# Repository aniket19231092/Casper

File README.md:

# Casper
Converting a telescope into one that automatically positions itself to view planets and other celestial bodies based on user input.
2 Stepper motor axis will position its azimuth, basically cardinal direction, and altitude, the angle between the horizon and straight up. To find the target a camera on the telescope tube will take pictures of the sky and use plate solving, which is where the position of the stars in the sky are compared to a database of known stars to find the coordinates of where in the sky the telescope is pointing. A Raspberry Pi will handle the bulk of the computing while a microcontroller drives the stepper motors. A belt system will be used to gain gear reduction between the stepper motors and the load shaft.
This project is split into 3 parts, mechanical, electrical, and software. On the electrical side I am making a custom PCB controller for the telescope. This includes a STM32 microcontroller, Raspberry Pi 0 2W, stepper motor drivers, power regulators, and all other supporting hardware.
The mechanical part will be designing a mechanical drive system for both axes out of commercially available parts and custom 3D printed parts.
On the software side, the Raspberry Pi will run the plate solving software and tell the microcontroller how much to move each motor. The Pi will also host an interface where user commands can be sent to operate the telescope.

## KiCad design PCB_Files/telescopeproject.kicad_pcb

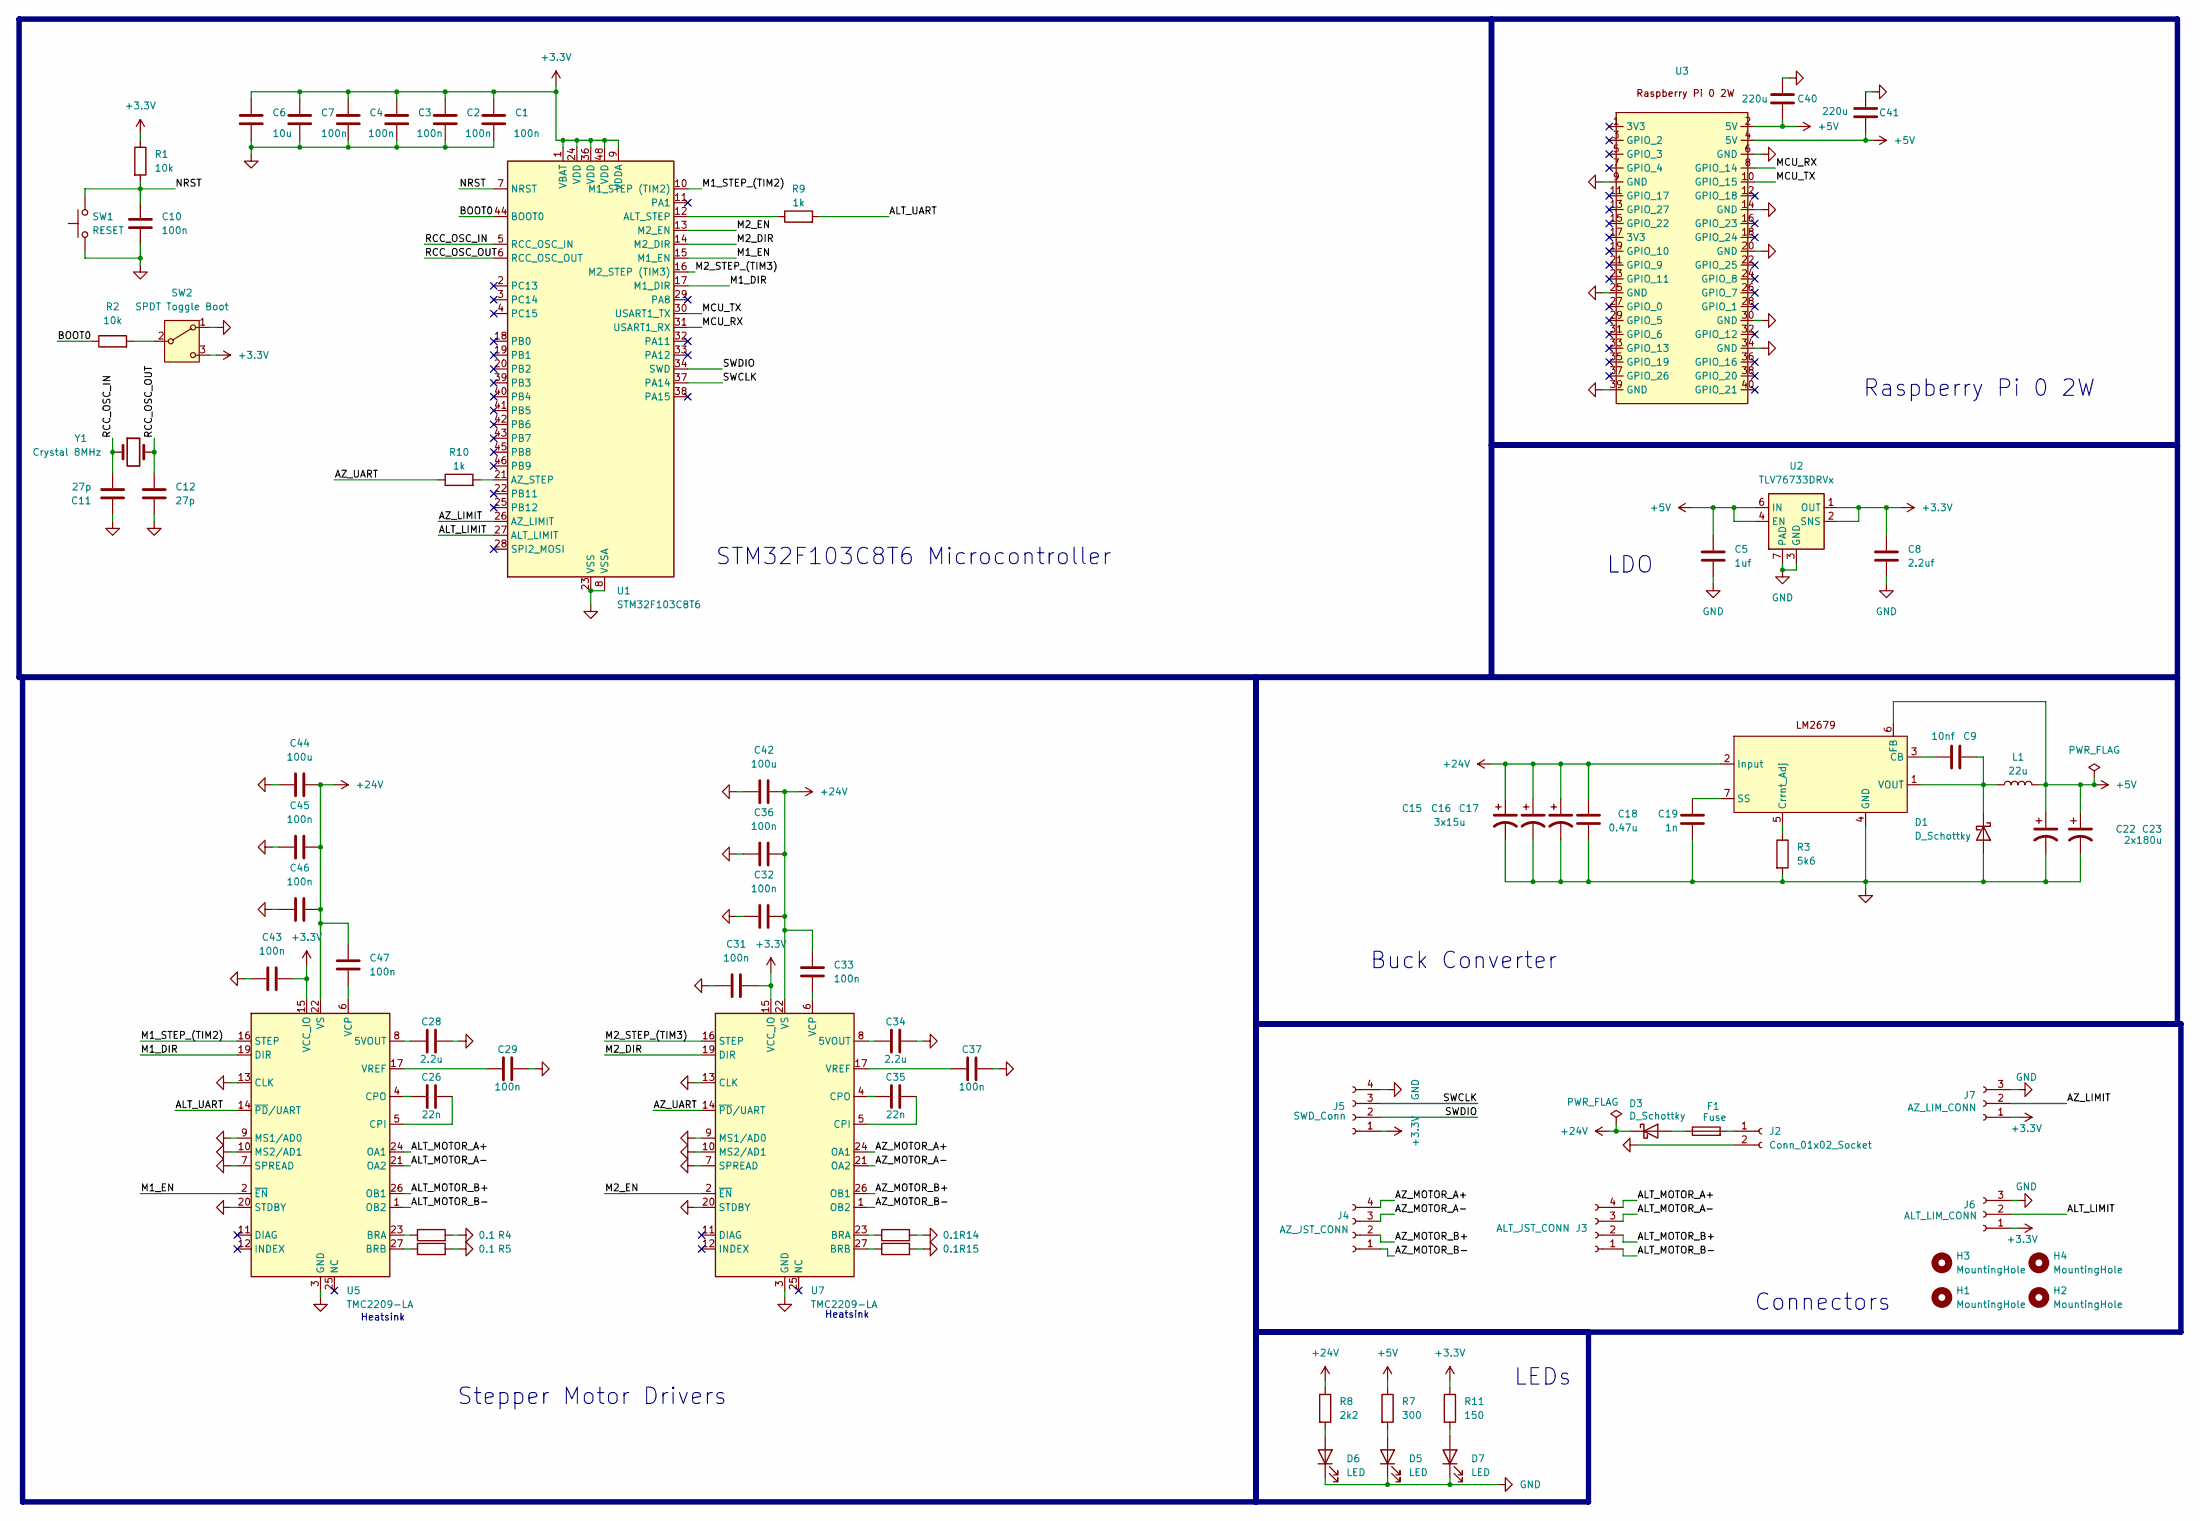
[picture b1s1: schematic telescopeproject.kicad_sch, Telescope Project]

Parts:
C1, C2, C3, C4, C7, C10, C29, C31, C32, C33, C36, C37, C43, C45, C46, C47: 100n; C_0603_1608Metric
C5: 1uf; C_1210_3225Metric
C6: 10u; C_Elec_5x5.4
C8: 2.2uf; C_1210_3225Metric
C9: 10nf; C_0603_1608Metric
C11, C12: 27p; C_0603_1608Metric
C15: 3x15u; CP_Elec_6.3x5.4
C16, C17: 15u; CP_Elec_6.3x5.4
C18: 0.47u; C_Elec_4x5.4
C19: 1n; C_0603_1608Metric
C22, C23: 2x180u; CP_Radial_D6.3mm_P2.50mm
C26, C35: 22n; C_0603_1608Metric
C28, C34: 2.2u; C_Elec_4x5.4
C40, C41: 220u; C_Radial_D10.0mm_H16.0mm_P5.00mm
C42, C44: 100u; C_Radial_D8.0mm_H7.0mm_P3.50mm
D1, D3: D_Schottky; TO-263-2
D5, D6, D7: LED; LED_0603_1608Metric
F1: Fuse; 30R800UH
H1, H2, H3, H4: MountingHole; MountingHole_3.2mm_M3_ISO14580_Pad
J2: Conn_01x02_Socket; B2PSVHLFSN
J3: ALT_JST_CONN; CONN_B4PS-VH_JST
J4: AZ_JST_CONN; CONN_B4PS-VH_JST
J5: SWD_Conn; PinHeader_1x04_P2.54mm_Horizontal
J6: ALT_LIM_CONN; CONN03_B3PS-VH_JST
J7: AZ_LIM_CONN; CONN03_B3PS-VH_JST
L1: 22u; D2PAK_STM
R1, R2: 10k; R_0603_1608Metric
R3: 5k6; R_0603_1608Metric
R4, R5, R14, R15: 0.1; R_2512_6332Metric
R7: 300; R_0603_1608Metric
R8: 2k2; R_0603_1608Metric
R9, R10: 1k; R_0603_1608Metric
R11: 150; R_0603_1608Metric
SW1: RESET; SW_PUSH_6mm_H4.3mm
SW2: SPDT Toggle Boot; PinHeader_1x03_P2.54mm_Vertical
U1: STM32F103C8T6; LQFP-48_7x7mm_P0.5mm
U2: TLV76733DRVx; WSON-6-1EP_2x2mm_P0.65mm_EP1x1.6mm_ThermalVias
U3: PinHeader_2x20_P2.54mm_Vertical
U5, U7: TMC2209-LA; VQFN-28-1EP_5x5mm_P0.5mm_EP3.7x3.7mm
U6: TO-220-7_P2.54x5.08mm_StaggerOdd_Lead3.08mm_Vertical
Y1: Crystal 8MHz; Crystal_SMD_Abracon_ABM3-2Pin_5.0x3.2mm

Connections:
+3.3V: C1.1, C2.1, C3.1, C4.1, C6.1, C7.1, C8.1, C31.2, C43.2, J5.1, J6.1, J7.1, R1.1, R11.1, SW2.3 (C), U1.1 (VBAT), U1.9 (VDDA), U1.24 (VDD), U1.36 (VDD), U1.48 (VDD), U2.1 (OUT), U2.2 (SNS), U5.15 (VCC_IO), U7.15 (VCC_IO)
+5V: C5.1, C22.1, C23.1, C40.2, C41.2, L1.2, R7.1, U2.4 (EN), U2.6 (IN), U3.2 (5V), U3.4 (5V), U6.6 (FB)
+24V: C15.1, C16.1, C17.1, C18.1, C32.2, C33.2, C36.2, C42.2, C44.2, C45.2, C46.2, C47.2, D3.1 (K), R8.1, U5.22 (VS), U5.28 (VS), U6.2 (Input), U7.22 (VS), U7.28 (VS)
/ALT_LIMIT: J6.2, U1.27 (ALT_LIMIT)
/ALT_MOTOR_A+: J3.4, U5.24 (OA1)
/ALT_MOTOR_A-: J3.3, U5.21 (OA2)
/ALT_MOTOR_B+: J3.2, U5.26 (OB1)
/ALT_MOTOR_B-: J3.1, U5.1 (OB2)
/ALT_UART: R9.2, U5.14 (~PD/UART)
/AZ_LIMIT: J7.2, U1.26 (AZ_LIMIT)
/AZ_MOTOR_A+: J4.4, U7.24 (OA1)
/AZ_MOTOR_A-: J4.3, U7.21 (OA2)
/AZ_MOTOR_B+: J4.2, U7.26 (OB1)
/AZ_MOTOR_B-: J4.1, U7.1 (OB2)
/AZ_UART: R10.1, U7.14 (~PD/UART)
/BOOT0: R2.1, U1.44 (BOOT0)
/M1_DIR: U1.17 (M1_DIR), U5.19 (DIR)
/M1_EN: U1.15 (M1_EN), U5.2 (~EN)
/M1_STEP_(TIM2): U1.10 (M1_STEP (TIM2)), U5.16 (STEP)
/M2_DIR: U1.14 (M2_DIR), U7.19 (DIR)
/M2_EN: U1.13 (M2_EN), U7.2 (~EN)
/M2_STEP_(TIM3): U1.16 (M2_STEP (TIM3)), U7.16 (STEP)
/MCU_RX: U1.31 (USART1_RX), U3.8 (GPIO_14)
/MCU_TX: U1.30 (USART1_TX), U3.10 (GPIO_15)
/NRST: C10.1, R1.2, SW1.2, U1.7 (NRST)
/RCC_OSC_IN: C11.2, U1.5 (RCC_OSC_IN), Y1.1
/RCC_OSC_OUT: C12.1, U1.6 (RCC_OSC_OUT), Y1.2
/SWCLK: J5.3, U1.37 (PA14)
/SWDIO: J5.2, U1.34 (SWD)
GND: C1.2, C2.2, C3.2, C4.2, C5.2, C6.2, C7.2, C8.2, C10.2, C11.1, C12.2, C15.2, C16.2, C17.2, C18.2, C19.2, C22.2, C23.2, C28.1, C29.1, C31.1, C32.1, C34.1, C36.1, C37.1, C40.1, C41.1, C42.1, C43.1, C44.1, C45.1, C46.1, D1.2 (A), D5.1 (K), D6.1 (K), D7.1 (K), J2.2, J5.4, J6.3, J7.3, R3.2, R4.2, R5.2, R14.2, R15.2, SW1.1, SW2.1 (A), U1.8 (VSSA), U1.23 (VSS), U1.35 (VSS), U1.47 (VSS), U2.3 (GND), U2.5 (GND), U2.7 (PAD), U3.6 (GND), U3.9 (GND), U3.14 (GND), U3.20 (GND), U3.25 (GND), U3.30 (GND), U3.34 (GND), U3.39 (GND), U5.3 (GND), U5.7 (SPREAD), U5.9 (MS1/AD0), U5.10 (MS2/AD1), U5.13 (CLK), U5.18 (GND), U5.20 (STDBY), U5.29 (GND), U6.4 (GND), U7.3 (GND), U7.7 (SPREAD), U7.9 (MS1/AD0), U7.10 (MS2/AD1), U7.13 (CLK), U7.18 (GND), U7.20 (STDBY), U7.29 (GND)
unnamed: C9.1, D1.1 (K), L1.1, U6.1 (VOUT)
unnamed: D3.2 (A), F1.1
unnamed: D5.2 (A), R7.2
unnamed: D6.2 (A), R8.2
unnamed: D7.2 (A), R11.2
unnamed: F1.2, J2.1
unnamed: R2.2, SW2.2 (B)
unnamed: R9.1, U1.12 (ALT_STEP)
unnamed: R10.2, U1.21 (AZ_STEP)
unnamed: C28.2, U5.8 (5VOUT)
unnamed: R4.1, U5.23 (BRA)
unnamed: R5.1, U5.27 (BRB)
unnamed: C26.1, U5.5 (CPI)
unnamed: C26.2, U5.4 (CPO)
unnamed: C47.1, U5.6 (VCP)
unnamed: C29.2, U5.17 (VREF)
unnamed: C9.2, U6.3 (CB)
unnamed: R3.1, U6.5 (Crrnt_Adj)
unnamed: C19.1, U6.7 (SS)
unnamed: C34.2, U7.8 (5VOUT)
unnamed: R14.1, U7.23 (BRA)
unnamed: R15.1, U7.27 (BRB)
unnamed: C35.1, U7.5 (CPI)
unnamed: C35.2, U7.4 (CPO)
unnamed: C33.1, U7.6 (VCP)
unnamed: C37.2, U7.17 (VREF)

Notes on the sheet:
LEDs
Stepper Motor Drivers
Raspberry Pi 0 2W
Heatsink
STM32F103C8T6 Microcontroller
LDO
Connectors
Buck Converter

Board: 2 copper layers, 71 parts (0 on the bottom side), 56 nets, no tracks yet.

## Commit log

2026-06-17 Enhance README with detailed project overview
    Expanded project description to include details on mechanical, electrical, and software components, as well as the role of the Raspberry Pi and custom PCB controller.
2026-06-17 Create firmware
2026-06-17 Create pcb
2026-06-17 Create cad
2026-06-17 Create assets
